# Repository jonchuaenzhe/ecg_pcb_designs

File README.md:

# EG3301R: Custom ECG Printed Circuit Board Designs

This repo contains the EAGLE files for the PCB design of a prototype double-lead ECG filter and amplifier as well as the final product: a compact 12-lead ECG filter and amplifier that has maximum dimensions of 70mm by 50mm. The pins S0 and S1 control the multiplexer that switches the input signal to the ECG monitor such that a ECG which comprises of 3 rows of 4 leads (plus 1 row of Lead 2) can be generated.

Picture of a Standard ECG

Board Design For 2-Lead ECG

Board Design For 12-Lead ECG

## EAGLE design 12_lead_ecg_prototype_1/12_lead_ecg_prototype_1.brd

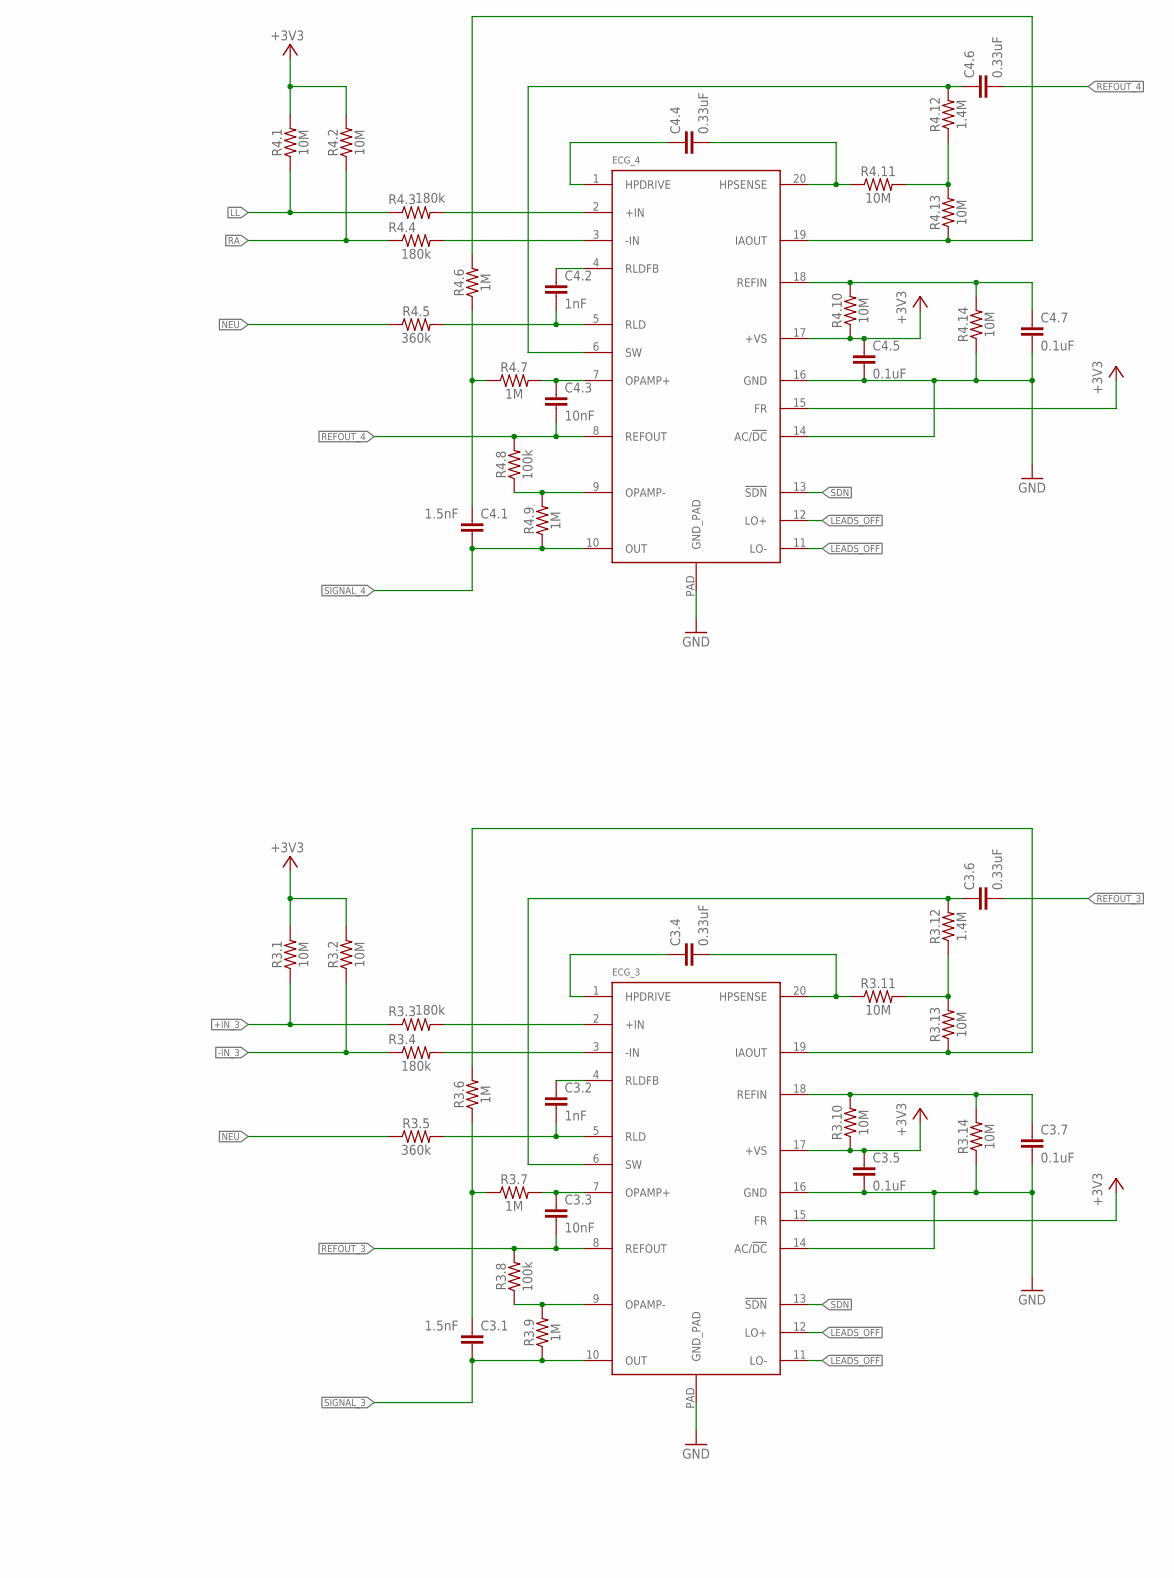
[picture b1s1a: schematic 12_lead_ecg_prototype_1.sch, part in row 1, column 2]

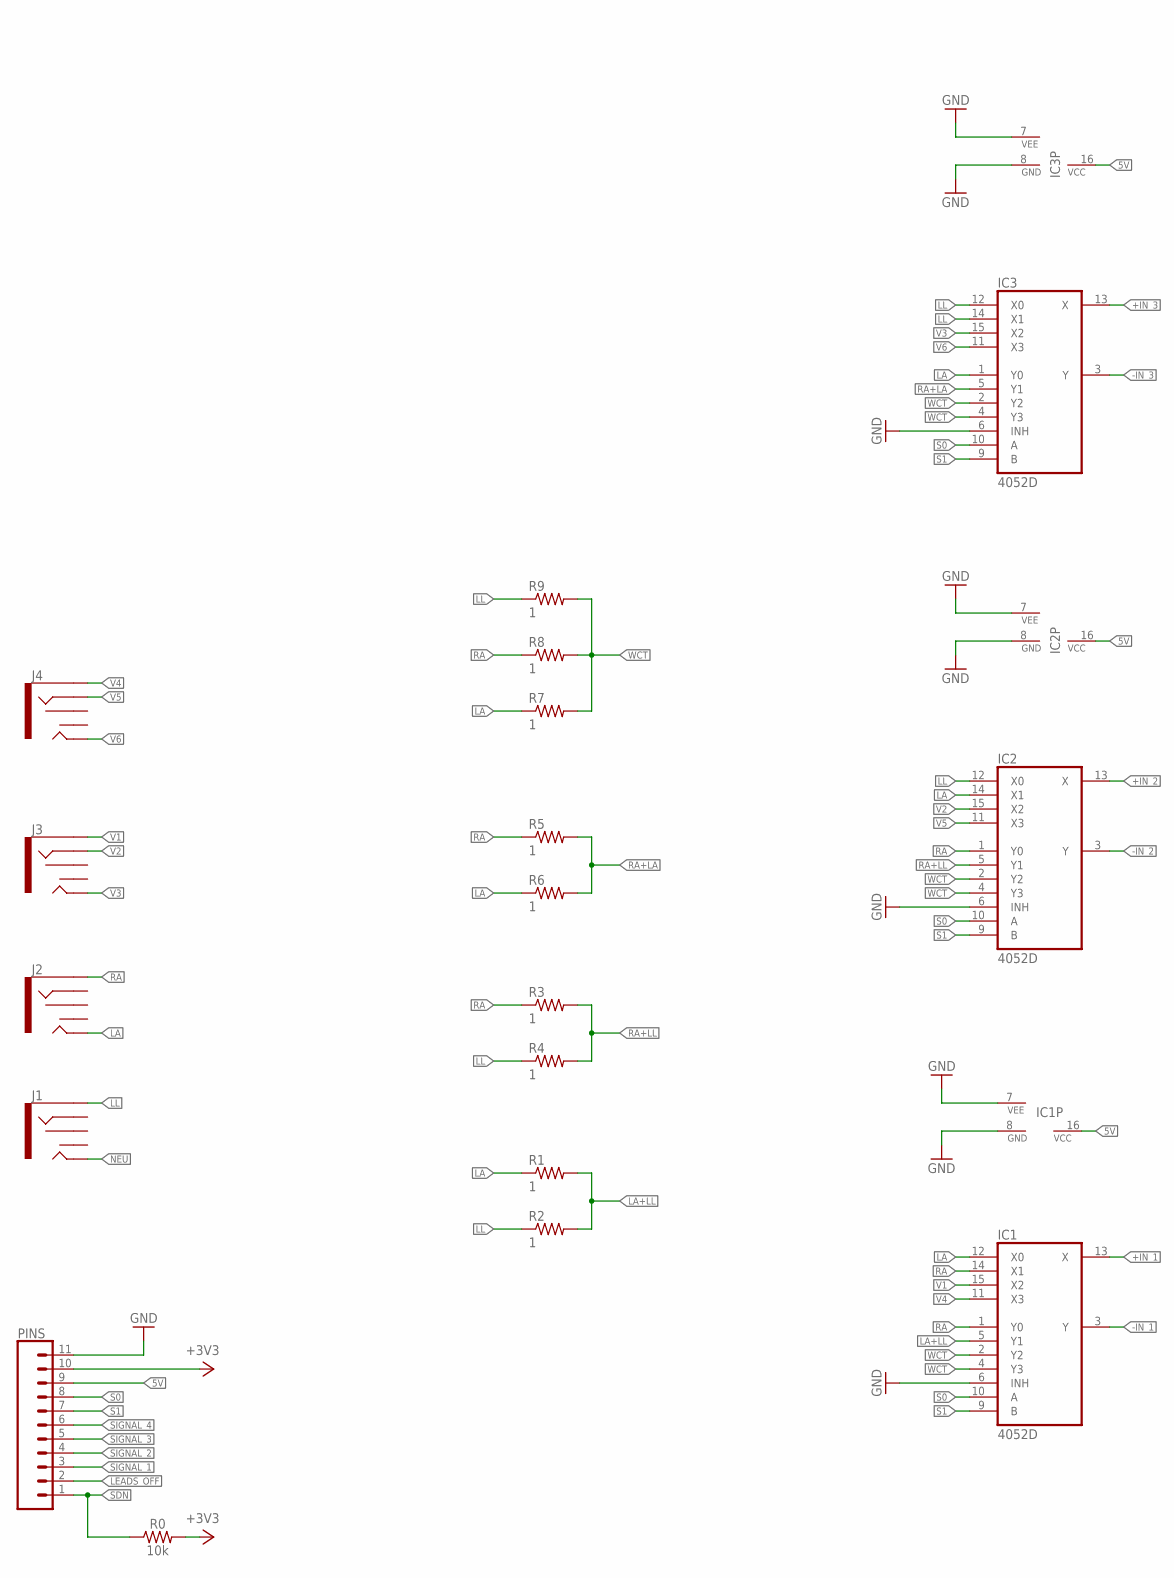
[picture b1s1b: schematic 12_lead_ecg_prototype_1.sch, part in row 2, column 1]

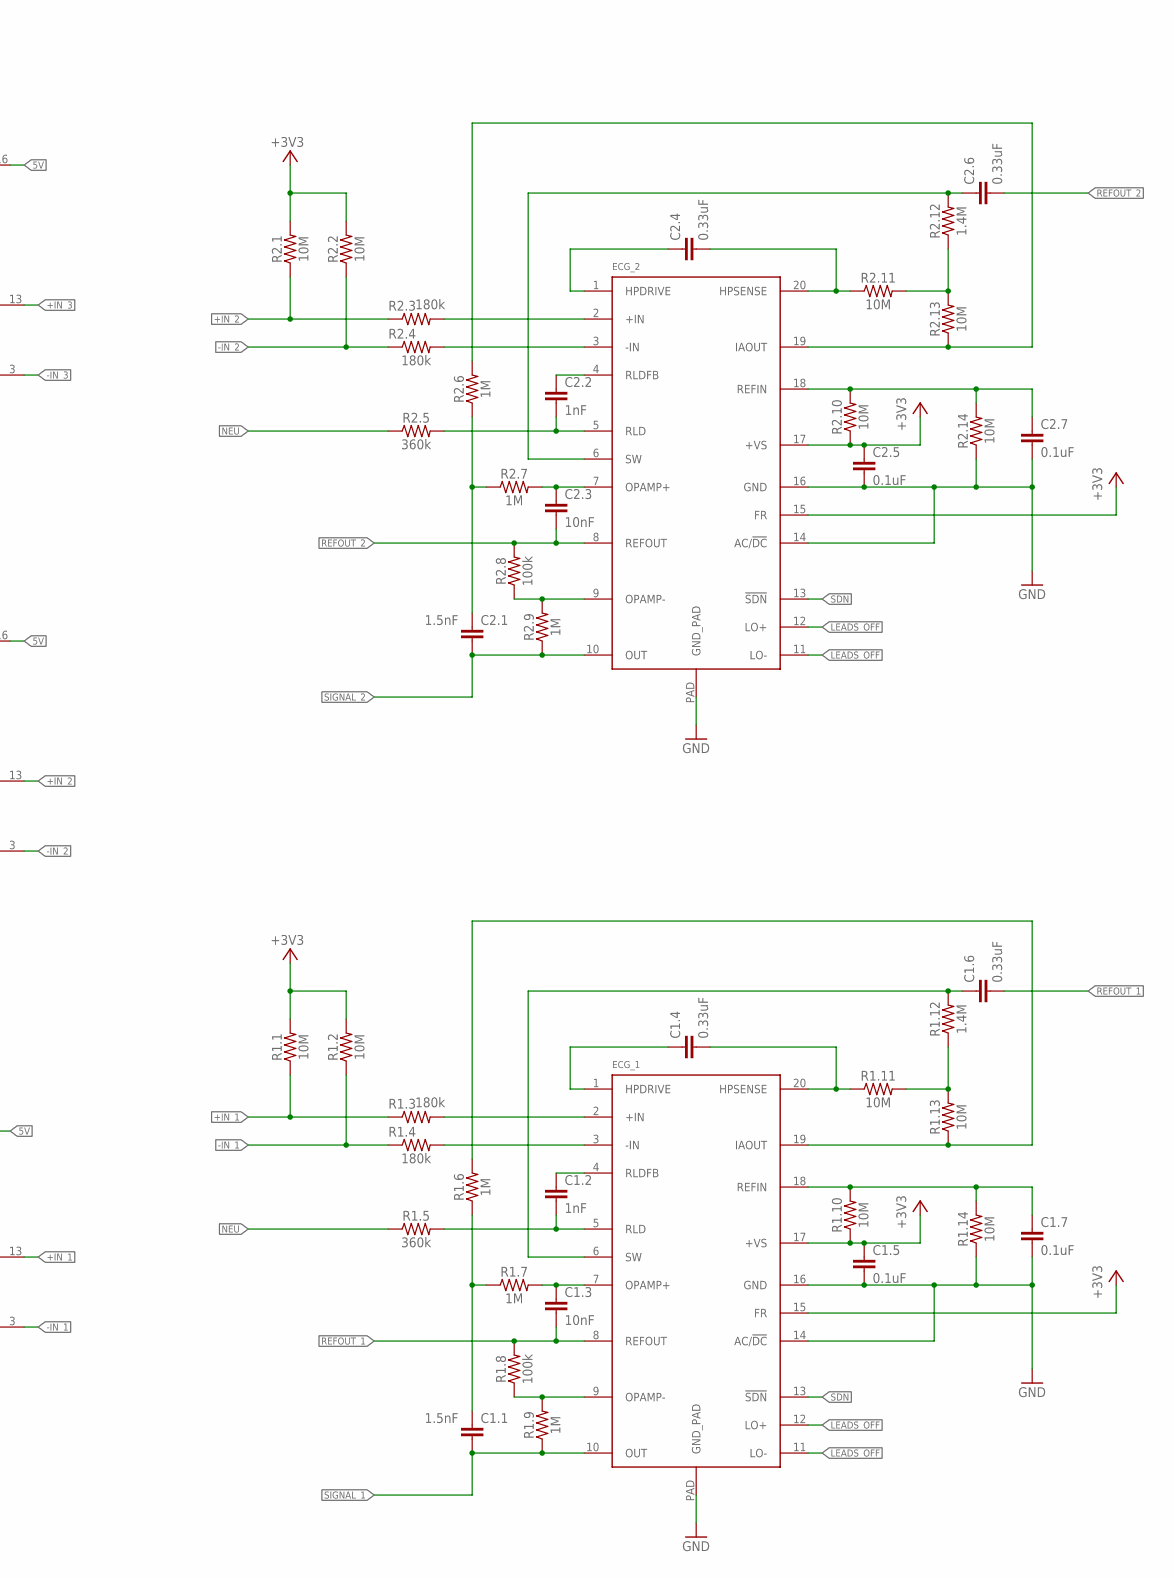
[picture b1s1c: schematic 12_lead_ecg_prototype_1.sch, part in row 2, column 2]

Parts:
C1.1, C2.1, C3.1, C4.1: 1.5nF; 0603-CAP
C1.2, C2.2, C3.2, C4.2: 1nF; 0603-CAP
C1.3, C2.3, C3.3, C4.3: 10nF; 0603-CAP
C1.4, C1.6, C2.4, C2.6, C3.4, C3.6, C4.4, C4.6: 0.33uF; 0805
C1.5, C1.7, C2.5, C2.7, C3.5, C3.7, C4.5, C4.7: 0.1uF; 0603-CAP
ECG_1, ECG_2, ECG_3, ECG_4: AD8232ACPZ-R7; LFCSP_20
IC1, IC2, IC3: 4052D; SO16
J1, J2, J3, J4: AUDIO_JACK_3.5MM_SMD; AUDIO-JACK-3.5MM-SMD
PINS: CONN_11; 1X11
R0: 10k; 0603
R1, R2, R3, R4, R5, R6, R7, R8, R9: 1; 0402-RES
R1.1, R1.2, R1.10, R1.11, R1.13, R1.14, R2.1, R2.2, R2.10, R2.11, R2.13, R2.14, R3.1, R3.2, R3.10, R3.11, R3.13, R3.14, R4.1, R4.2, R4.10, R4.11, R4.13, R4.14: 10M; 0603
R1.3, R1.4, R2.3, R2.4, R3.3, R3.4, R4.3, R4.4: 180k; 0603
R1.5, R2.5, R3.5, R4.5: 360k; 0603
R1.6, R1.7, R1.9, R2.6, R2.7, R2.9, R3.6, R3.7, R3.9, R4.6, R4.7, R4.9: 1M; 0603
R1.8, R2.8, R3.8, R4.8: 100k; 0603
R1.12, R2.12, R3.12, R4.12: 1.4M; 0603

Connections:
5V: IC1.16 (VCC), IC2.16 (VCC), IC3.16 (VCC), PINS.9
+3V3: C1.5.1, C2.5.1, C3.5.1, C4.5.1, ECG_1.15 (FR), ECG_1.17 (+VS), ECG_2.15 (FR), ECG_2.17 (+VS), ECG_3.15 (FR), ECG_3.17 (+VS), ECG_4.15 (FR), ECG_4.17 (+VS), PINS.10, R0.2, R1.1.2, R1.2.2, R1.10.1, R2.1.2, R2.2.2, R2.10.1, R3.1.2, R3.2.2, R3.10.1, R4.1.2, R4.2.2, R4.10.1
+IN_1: IC1.13 (X), R1.1.1, R1.3.1
+IN_2: IC2.13 (X), R2.1.1, R2.3.1
+IN_3: IC3.13 (X), R3.1.1, R3.3.1
-IN_1: IC1.3 (Y), R1.2.1, R1.4.1
-IN_2: IC2.3 (Y), R2.2.1, R2.4.1
-IN_3: IC3.3 (Y), R3.2.1, R3.4.1
GND: C1.5.2, C1.7.2, C2.5.2, C2.7.2, C3.5.2, C3.7.2, C4.5.2, C4.7.2, ECG_1.14 (AC/!DC), ECG_1.16 (GND), ECG_1.PAD (GND_PAD), ECG_2.14 (AC/!DC), ECG_2.16 (GND), ECG_2.PAD (GND_PAD), ECG_3.14 (AC/!DC), ECG_3.16 (GND), ECG_3.PAD (GND_PAD), ECG_4.14 (AC/!DC), ECG_4.16 (GND), ECG_4.PAD (GND_PAD), IC1.6 (INH), IC1.7 (VEE), IC1.8 (GND), IC2.6 (INH), IC2.7 (VEE), IC3.6 (INH), IC3.7 (VEE), PINS.11, R1.14.1, R2.14.1, R3.14.1, R4.14.1
LA: IC1.12 (X0), IC2.14 (X1), IC3.1 (Y0), J2.TIP, R1.1, R6.1, R7.1
LA+LL: IC1.5 (Y1), R1.2, R2.2
LEADS_OFF: ECG_1.11 (LO-), ECG_1.12 (LO+), ECG_2.11 (LO-), ECG_2.12 (LO+), ECG_3.11 (LO-), ECG_3.12 (LO+), ECG_4.11 (LO-), ECG_4.12 (LO+), PINS.2
LL: IC2.12 (X0), IC3.12 (X0), IC3.14 (X1), J1.SLEEVE, R2.1, R4.1, R4.1.1, R4.3.1, R9.1
unnamed: ECG_1.9 (OPAMP-), R1.8.1, R1.9.2
unnamed: ECG_2.2 (+IN), R2.3.2
unnamed: ECG_1.2 (+IN), R1.3.2
unnamed: ECG_1.3 (-IN), R1.4.2
unnamed: ECG_2.3 (-IN), R2.4.2
unnamed: C1.1.1, R1.6.1, R1.7.1
unnamed: C1.3.1, ECG_1.7 (OPAMP+), R1.7.2
unnamed: C1.2.1, ECG_1.4 (RLDFB)
unnamed: C1.2.2, ECG_1.5 (RLD), R1.5.2
unnamed: ECG_1.19 (IAOUT), R1.6.2, R1.13.1
unnamed: C1.6.1, ECG_1.6 (SW), R1.12.2
unnamed: C1.7.1, ECG_1.18 (REFIN), R1.10.2, R1.14.2
unnamed: R1.11.2, R1.12.1, R1.13.2
unnamed: C1.4.2, ECG_1.20 (HPSENSE), R1.11.1
unnamed: C1.4.1, ECG_1.1 (HPDRIVE)
unnamed: C2.2.1, ECG_2.4 (RLDFB)
unnamed: C2.2.2, ECG_2.5 (RLD), R2.5.2
unnamed: IC2.8 (GND), IC3.8 (GND)
unnamed: C2.1.1, R2.6.1, R2.7.1
unnamed: C2.3.1, ECG_2.7 (OPAMP+), R2.7.2
unnamed: ECG_2.9 (OPAMP-), R2.8.1, R2.9.2
unnamed: ECG_2.19 (IAOUT), R2.6.2, R2.13.1
unnamed: C2.6.1, ECG_2.6 (SW), R2.12.2
unnamed: R2.11.2, R2.12.1, R2.13.2
unnamed: C2.4.2, ECG_2.20 (HPSENSE), R2.11.1
unnamed: C2.4.1, ECG_2.1 (HPDRIVE)
unnamed: C2.7.1, ECG_2.18 (REFIN), R2.10.2, R2.14.2
unnamed: ECG_3.2 (+IN), R3.3.2
unnamed: ECG_3.3 (-IN), R3.4.2
unnamed: C3.2.1, ECG_3.4 (RLDFB)
unnamed: C3.2.2, ECG_3.5 (RLD), R3.5.2
unnamed: C3.1.1, R3.6.1, R3.7.1
unnamed: C3.3.1, ECG_3.7 (OPAMP+), R3.7.2
unnamed: ECG_3.9 (OPAMP-), R3.8.1, R3.9.2
unnamed: ECG_3.19 (IAOUT), R3.6.2, R3.13.1
unnamed: C3.6.1, ECG_3.6 (SW), R3.12.2
unnamed: R3.11.2, R3.12.1, R3.13.2
unnamed: C3.4.2, ECG_3.20 (HPSENSE), R3.11.1
unnamed: C3.4.1, ECG_3.1 (HPDRIVE)
unnamed: C3.7.1, ECG_3.18 (REFIN), R3.10.2, R3.14.2
unnamed: ECG_4.2 (+IN), R4.3.2
unnamed: ECG_4.3 (-IN), R4.4.2
unnamed: C4.2.1, ECG_4.4 (RLDFB)
unnamed: C4.2.2, ECG_4.5 (RLD), R4.5.2
unnamed: C4.1.1, R4.6.1, R4.7.1
unnamed: C4.3.1, ECG_4.7 (OPAMP+), R4.7.2
unnamed: ECG_4.9 (OPAMP-), R4.8.1, R4.9.2
unnamed: ECG_4.19 (IAOUT), R4.6.2, R4.13.1
unnamed: C4.6.1, ECG_4.6 (SW), R4.12.2
unnamed: R4.11.2, R4.12.1, R4.13.2
unnamed: C4.4.2, ECG_4.20 (HPSENSE), R4.11.1
unnamed: C4.4.1, ECG_4.1 (HPDRIVE)
unnamed: C4.7.1, ECG_4.18 (REFIN), R4.10.2, R4.14.2
NEU: J1.TIP, R1.5.1, R2.5.1, R3.5.1, R4.5.1
RA: IC1.1 (Y0), IC1.14 (X1), IC2.1 (Y0), J2.SLEEVE, R3.1, R4.2.1, R4.4.1, R5.1, R8.1
RA+LA: IC3.5 (Y1), R5.2, R6.2
RA+LL: IC2.5 (Y1), R3.2, R4.2
REFOUT_1: C1.3.2, C1.6.2, ECG_1.8 (REFOUT), R1.8.2
REFOUT_2: C2.3.2, C2.6.2, ECG_2.8 (REFOUT), R2.8.2
REFOUT_3: C3.3.2, C3.6.2, ECG_3.8 (REFOUT), R3.8.2
REFOUT_4: C4.3.2, C4.6.2, ECG_4.8 (REFOUT), R4.8.2
S0: IC1.10 (A), IC2.10 (A), IC3.10 (A), PINS.8
S1: IC1.9 (B), IC2.9 (B), IC3.9 (B), PINS.7
SDN: ECG_1.13 (!SDN), ECG_2.13 (!SDN), ECG_3.13 (!SDN), ECG_4.13 (!SDN), PINS.1, R0.1
SIGNAL_1: C1.1.2, ECG_1.10 (OUT), PINS.3, R1.9.1
SIGNAL_2: C2.1.2, ECG_2.10 (OUT), PINS.4, R2.9.1
SIGNAL_3: C3.1.2, ECG_3.10 (OUT), PINS.5, R3.9.1
SIGNAL_4: C4.1.2, ECG_4.10 (OUT), PINS.6, R4.9.1
V1: IC1.15 (X2), J3.SLEEVE
V2: IC2.15 (X2), J3.RING
V3: IC3.15 (X2), J3.TIP
V4: IC1.11 (X3), J4.SLEEVE
V5: IC2.11 (X3), J4.RING
V6: IC3.11 (X3), J4.TIP
WCT: IC1.2 (Y2), IC1.4 (Y3), IC2.2 (Y2), IC2.4 (Y3), IC3.2 (Y2), IC3.4 (Y3), R7.2, R8.2, R9.2

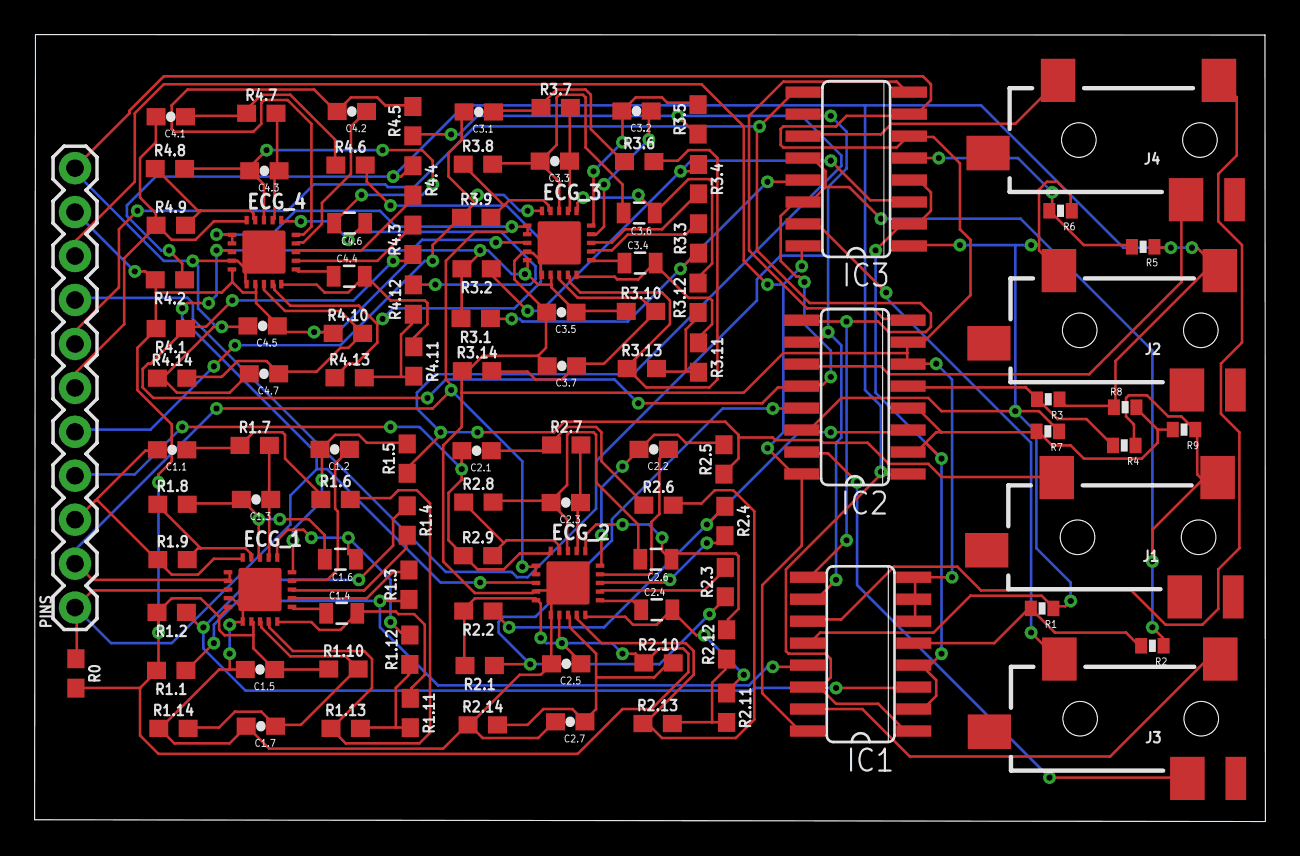
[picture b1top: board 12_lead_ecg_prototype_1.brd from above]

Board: 2 copper layers, 71.2 x 45.5 mm, 106 parts (0 on the bottom side), 88 nets.

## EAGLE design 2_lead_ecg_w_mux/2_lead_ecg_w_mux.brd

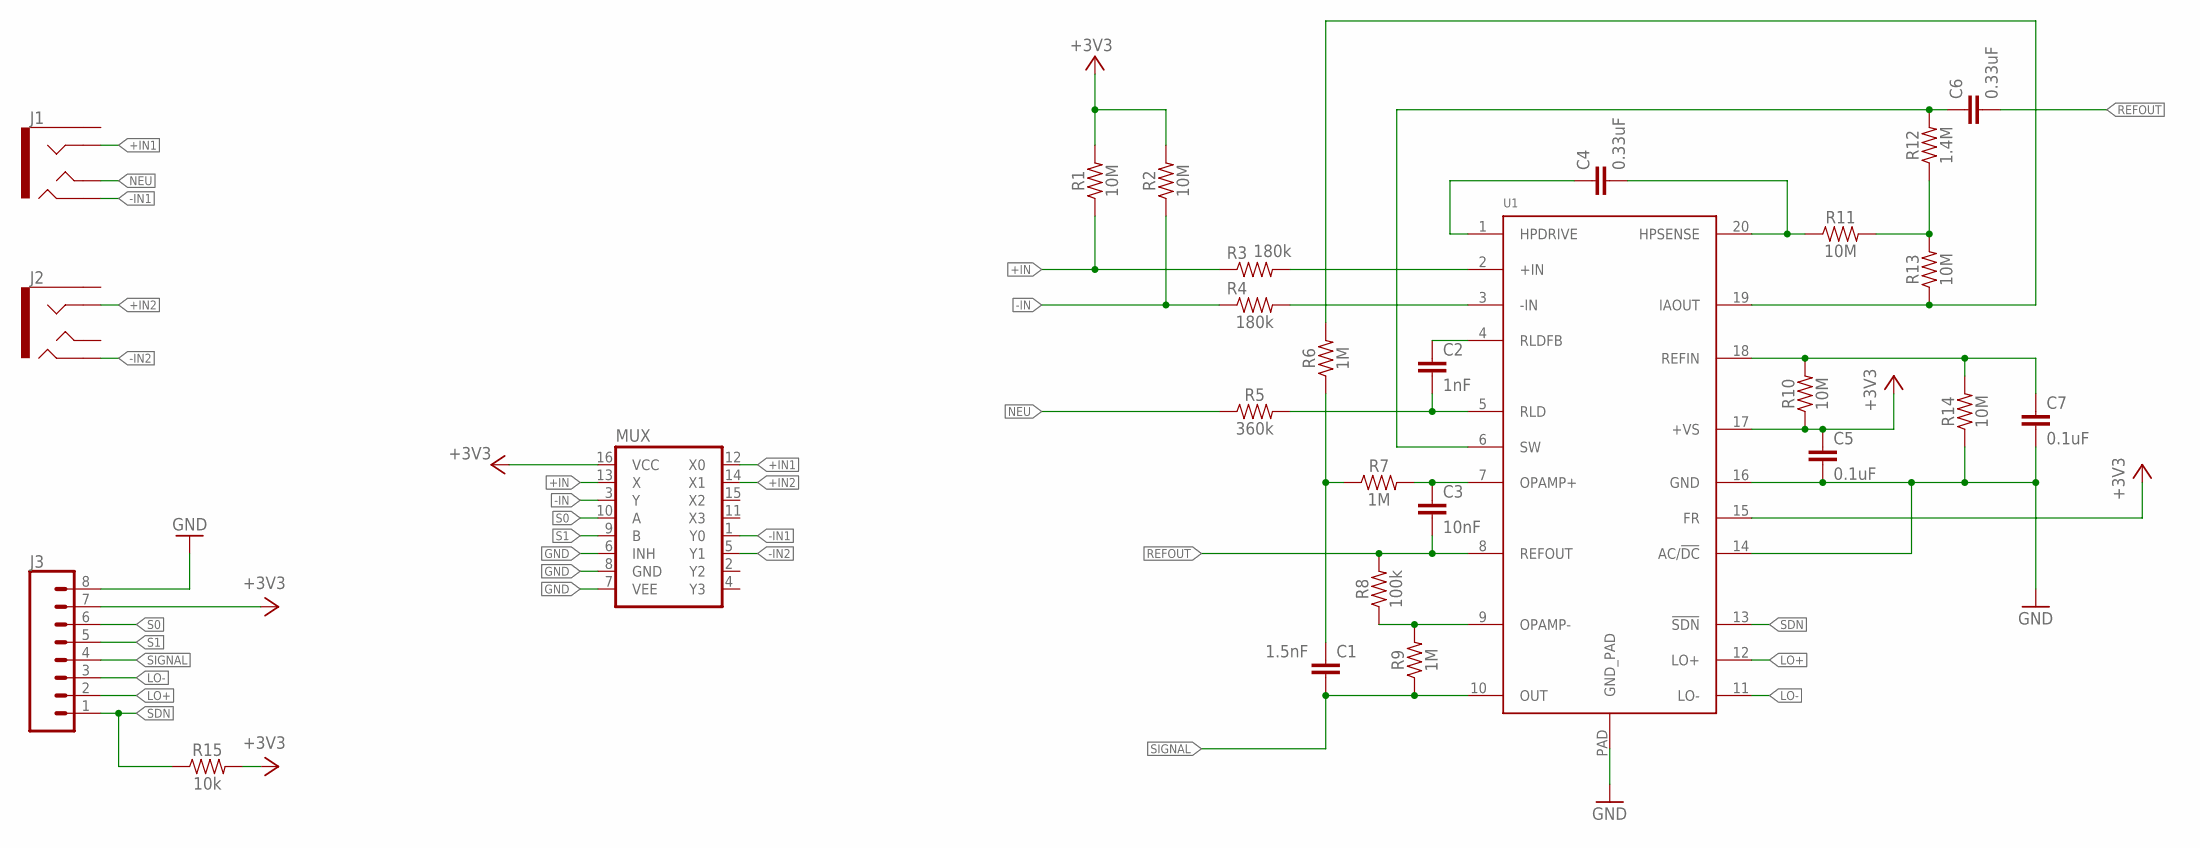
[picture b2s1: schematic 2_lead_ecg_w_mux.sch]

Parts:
C1: 1.5nF; 0603-CAP
C2: 1nF; 0603-CAP
C3: 10nF; 0603-CAP
C4, C6: 0.33uF; 0805
C5, C7: 0.1uF; 0603-CAP
J1, J2: AUDIO_JACK_TRRSSMD_RA; AUDIO_JACK_3.5MM_TRRS_SMD_RA
J3: CONN_08"; 1X08
MUX: 74HC4052D; SO16
R1, R2, R10, R11, R13, R14: 10M; 0603
R3, R4: 180k; 0603
R5: 360k; 0603
R6, R7, R9: 1M; 0603
R8: 100k; 0603
R12: 1.4M; 0603
R15: 10k; 0603
U1: AD8232ACPZ-R7; LFCSP_20

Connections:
+3V3: C5.1, J3.7, MUX.16 (VCC), R1.2, R2.2, R10.1, R15.2, U1.15 (FR), U1.17 (+VS)
+IN: MUX.13 (X), R1.1, R3.1
+IN1: J1.RING1, MUX.12 (X0)
+IN2: J2.RING1, MUX.14 (X1)
-IN: MUX.3 (Y), R2.1, R4.1
-IN1: J1.RING2, MUX.1 (Y0)
-IN2: J2.RING2, MUX.5 (Y1)
GND: C5.2, C7.2, J3.8, MUX.6 (INH), MUX.7 (VEE), MUX.8 (GND), R14.1, U1.14 (AC/!DC), U1.16 (GND), U1.PAD (GND_PAD)
LO+: J3.2, U1.12 (LO+)
LO-: J3.3, U1.11 (LO-)
unnamed: R8.1, R9.2, U1.9 (OPAMP-)
unnamed: R3.2, U1.2 (+IN)
unnamed: R4.2, U1.3 (-IN)
unnamed: C1.1, R6.1, R7.1
unnamed: C3.1, R7.2, U1.7 (OPAMP+)
unnamed: C2.1, U1.4 (RLDFB)
unnamed: C2.2, R5.2, U1.5 (RLD)
unnamed: R6.2, R13.1, U1.19 (IAOUT)
unnamed: C6.1, R12.2, U1.6 (SW)
unnamed: C7.1, R10.2, R14.2, U1.18 (REFIN)
unnamed: R11.2, R12.1, R13.2
unnamed: C4.2, R11.1, U1.20 (HPSENSE)
unnamed: C4.1, U1.1 (HPDRIVE)
NEU: J1.TIP, R5.1
REFOUT: C3.2, C6.2, R8.2, U1.8 (REFOUT)
S0: J3.6, MUX.10 (A)
S1: J3.5, MUX.9 (B)
SDN: J3.1, R15.1, U1.13 (!SDN)
SIGNAL: C1.2, J3.4, R9.1, U1.10 (OUT)

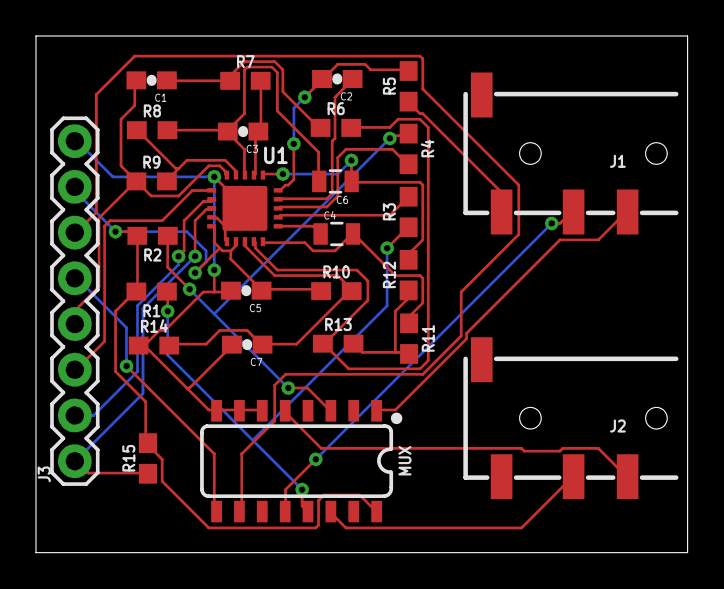
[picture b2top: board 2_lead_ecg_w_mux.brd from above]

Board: 2 copper layers, 36.2 x 28.7 mm, 27 parts (0 on the bottom side), 29 nets.

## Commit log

2020-08-18 added files
2020-08-18 added pics
2020-08-18 add sample ecg

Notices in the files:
parts and their libraries:
SparkFun-Passives: Licensing: CC v3.0 Share-Alike You are welcome to use this library for commercial purposes.
SparkFun-Sensors: Licensing: Creative Commons ShareAlike 4.0 International - https://creativecommons.org/licenses/by-sa/4.0
